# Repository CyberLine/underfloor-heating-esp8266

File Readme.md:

# ESP8266 WiFi based underfloor heating control

### Hardware

See: [Hardware.md](Hardware.md)

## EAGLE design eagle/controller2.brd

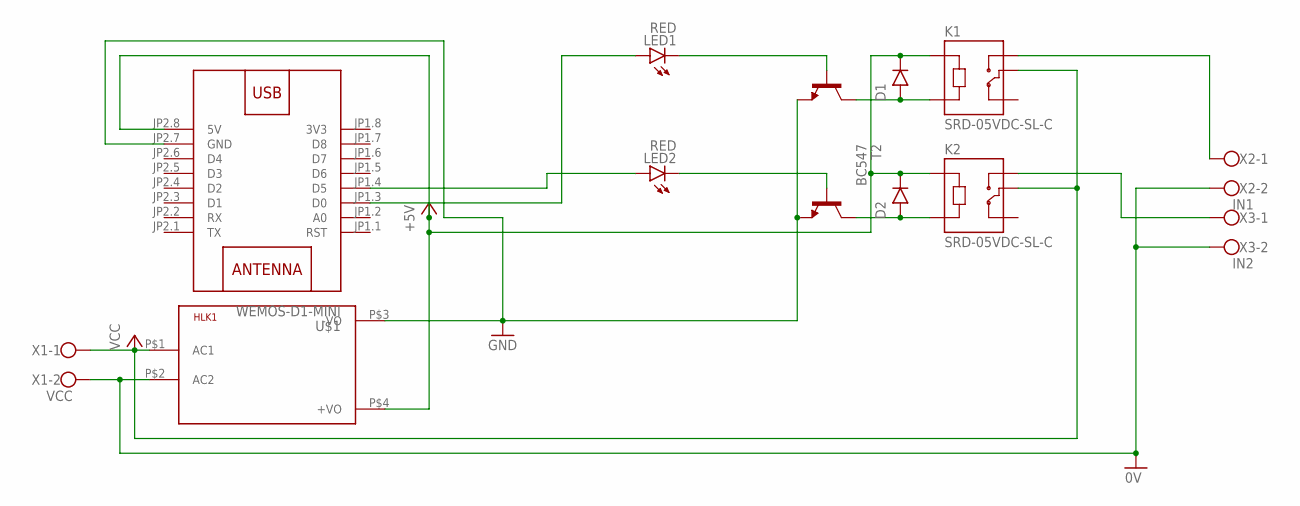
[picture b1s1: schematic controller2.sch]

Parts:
D1, D2: 1N4001; DO41-10
HLK1: HLK-PM013W; HLK-PM01
K1, K2: SRD-05VDC-SL-C; RELAY_SRD-05VDC-SL-C
LED1, LED2: RED; LED3MM
T1, T2: BC547; TO92
U$1: WEMOS-D1-MINI
X1: VCC; W237-102
X2: IN1; W237-102
X3: IN2; W237-102

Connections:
0V: HLK1.P$2 (AC2), X1.2, X2.2, X3.2
3V3: U$1.JP1.8 (3V3)
+5V: D1.C (CATHODE), D2.C (CATHODE), HLK1.P$4 (+VO), K1.A1, K2.A1, U$1.JP2.8 (5V)
GND: HLK1.P$3 (-VO), T1.1 (E), T2.1 (E), U$1.JP2.7 (GND)
unnamed: D1.A (ANODE), K1.A2, T1.3 (C)
unnamed: K1.NO, X2.1
unnamed: D2.A (ANODE), K2.A2, T2.3 (C)
unnamed: LED2.K (C), T2.2 (B)
unnamed: LED1.K (C), T1.2 (B)
unnamed: K2.NO, X3.1
unnamed: LED2.A, U$1.JP1.4 (D5)
unnamed: LED1.A, U$1.JP1.3 (D0)
VCC: HLK1.P$1 (AC1), K1.COM, K2.COM, X1.1

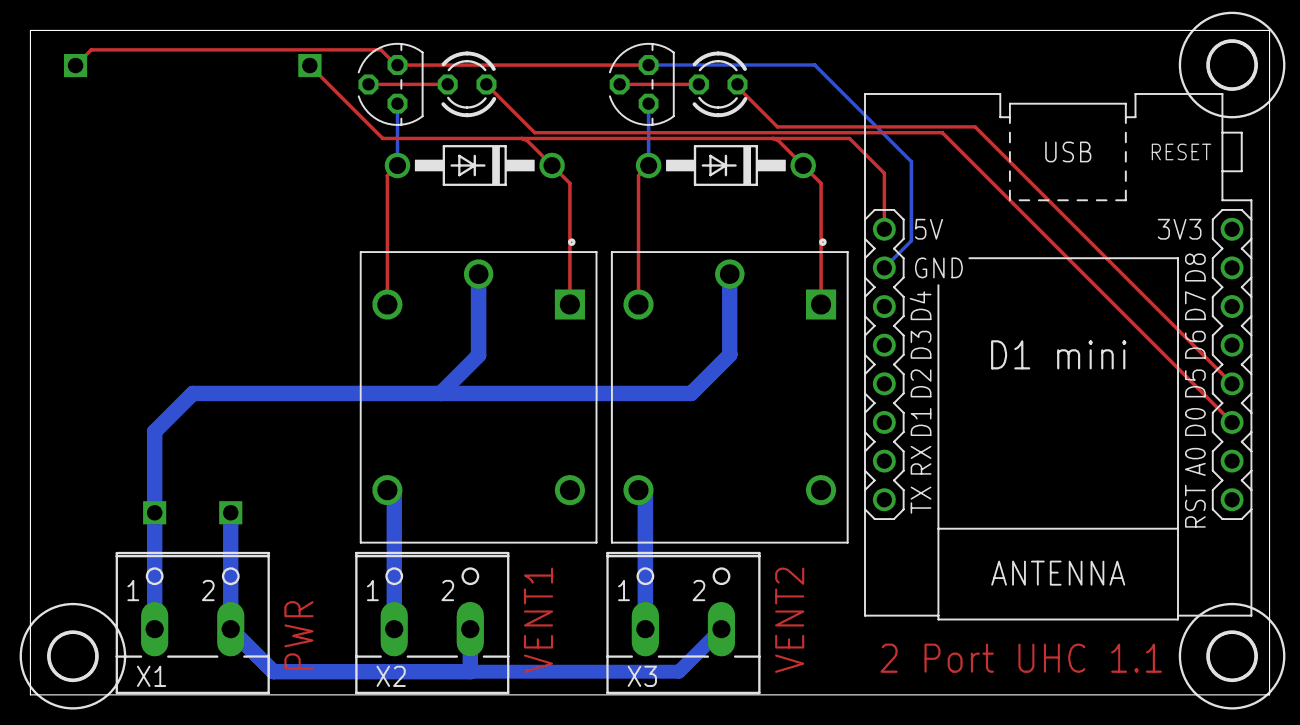
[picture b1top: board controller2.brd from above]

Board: 2 copper layers, 81.5 x 43.7 mm, 16 parts (0 on the bottom side), 12 nets.

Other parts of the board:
U$2, U$3, U$4: 3,0

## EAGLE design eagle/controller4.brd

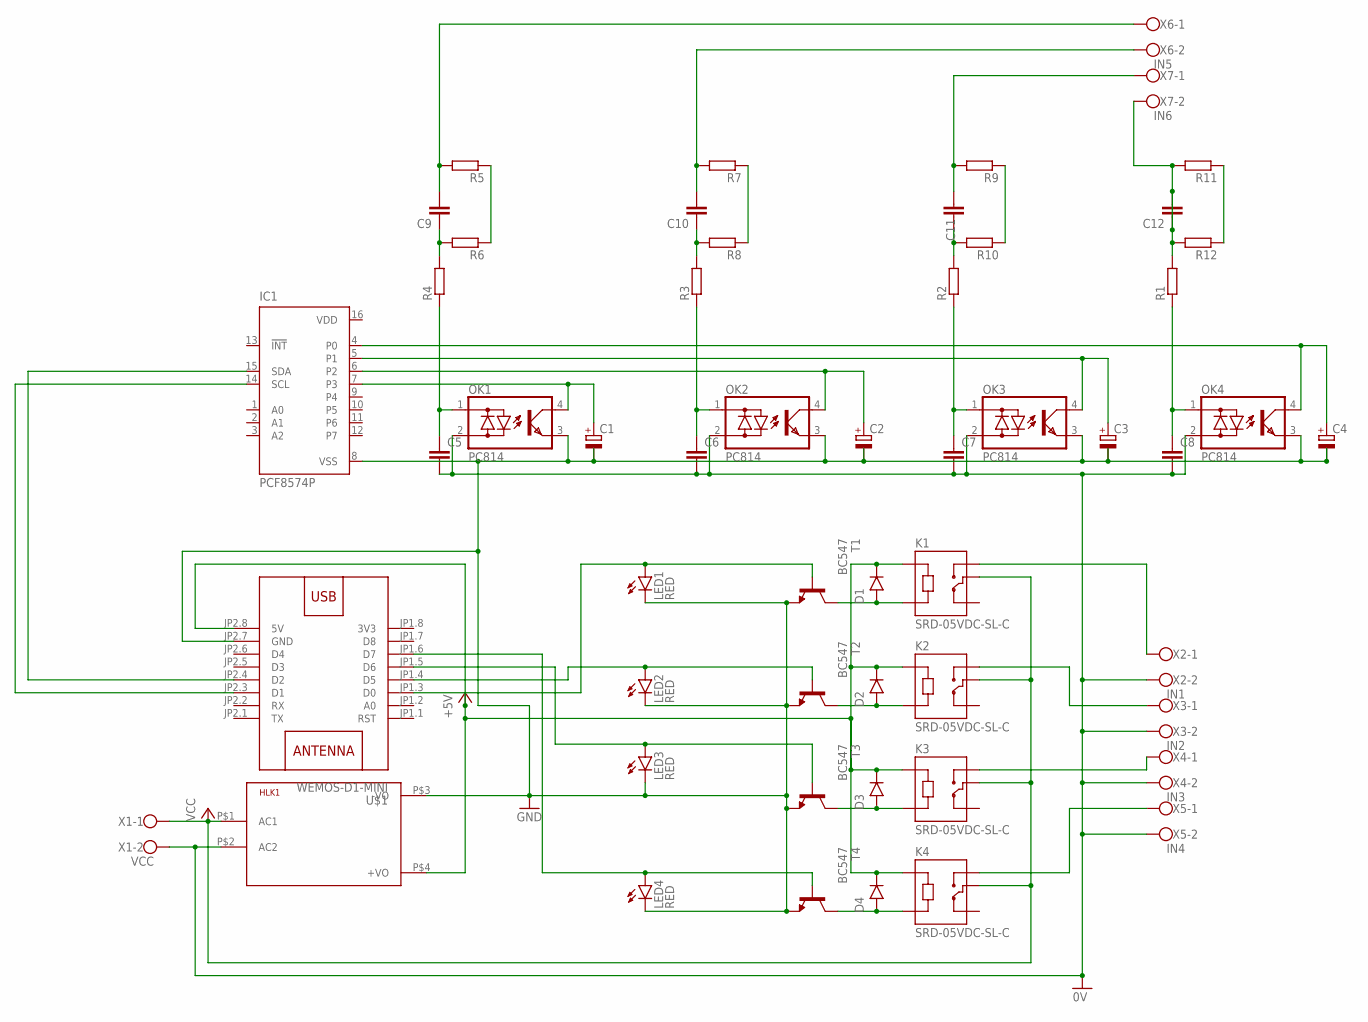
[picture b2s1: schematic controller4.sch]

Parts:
C1, C2, C3, C4: CPOL-EUE5-5; E5-5
C5, C6, C7, C8, C9, C10, C11, C12: C-EU025-024X044; C025-024X044
D1, D2, D3, D4: 1N4001; DO41-10
HLK1: HLK-PM013W; HLK-PM01
IC1: PCF8574P; DIL16
K1, K2, K3, K4: SRD-05VDC-SL-C; RELAY_SRD-05VDC-SL-C
LED1, LED2, LED3, LED4: RED; LED3MM
OK1, OK2, OK3, OK4: PC814; DIL04
R1, R2, R3, R4, R5, R6, R7, R8, R9, R10, R11, R12: R-EU_0204/5; 0204/5
T1, T2, T3, T4: BC547; TO92
U$1: WEMOS-D1-MINI
X1: VCC; W237-102
X2: IN1; W237-102
X3: IN2; W237-102
X4: IN3; W237-102
X5: IN4; W237-102
X6: IN5; W237-102
X7: IN6; W237-102

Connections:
0V: C5.2, C6.2, C7.2, C8.2, HLK1.P$2 (AC2), OK1.2 (AC2), OK2.2 (AC2), OK3.2 (AC2), OK4.2 (AC2), X1.2, X2.2, X3.2, X4.2, X5.2
3V3: U$1.JP1.8 (3V3)
+5V: D1.C (CATHODE), D2.C (CATHODE), D3.C (CATHODE), D4.C (CATHODE), HLK1.P$4 (+VO), K1.A1, K2.A1, K3.A1, K4.A1, U$1.JP2.8 (5V)
GND: C1.-, C2.-, C3.-, C4.-, HLK1.P$3 (-VO), IC1.8 (VSS), LED1.K (C), LED2.K (C), LED3.K (C), LED4.K (C), OK1.3 (E), OK2.3 (E), OK3.3 (E), OK4.3 (E), T1.1 (E), T2.1 (E), T3.1 (E), T4.1 (E), U$1.JP2.7 (GND)
unnamed: D1.A (ANODE), K1.A2, T1.3 (C)
unnamed: K1.NO, X2.1
unnamed: D2.A (ANODE), K2.A2, T2.3 (C)
unnamed: D3.A (ANODE), K3.A2, T3.3 (C)
unnamed: D4.A (ANODE), K4.A2, T4.3 (C)
unnamed: C1.+, IC1.7 (P3), OK1.4 (C)
unnamed: C2.+, IC1.6 (P2), OK2.4 (C)
unnamed: C3.+, IC1.5 (P1), OK3.4 (C)
unnamed: C4.+, IC1.4 (P0), OK4.4 (C)
unnamed: C9.1, R4.2, R6.2
unnamed: K2.NO, X3.1
unnamed: K3.NO, X4.1
unnamed: K4.NO, X5.1
unnamed: LED2.A, T2.2 (B), U$1.JP1.4 (D5)
unnamed: LED1.A, T1.2 (B), U$1.JP1.3 (D0)
unnamed: LED4.A, T4.2 (B), U$1.JP1.6 (D7)
unnamed: IC1.14 (SCL), U$1.JP2.3 (D1)
unnamed: IC1.15 (SDA), U$1.JP2.4 (D2)
unnamed: LED3.A, T3.2 (B), U$1.JP1.5 (D6)
unnamed: C10.1, R3.2, R8.2
unnamed: C11.1, R2.2, R10.2
unnamed: C8.1, OK4.1 (AC1), R1.1
unnamed: C11.2, R9.2, X7.1
unnamed: C10.2, R7.2, X6.2
unnamed: C9.2, R5.2, X6.1
unnamed: R5.1, R6.1
unnamed: C12.1, C12.2, R1.2, R11.2, R12.2, X7.2
unnamed: C7.1, OK3.1 (AC1), R2.1
unnamed: C6.1, OK2.1 (AC1), R3.1
unnamed: C5.1, OK1.1 (AC1), R4.1
unnamed: R7.1, R8.1
unnamed: R9.1, R10.1
unnamed: R11.1, R12.1
VCC: HLK1.P$1 (AC1), K1.COM, K2.COM, K3.COM, K4.COM, X1.1
VDD: IC1.16 (VDD)

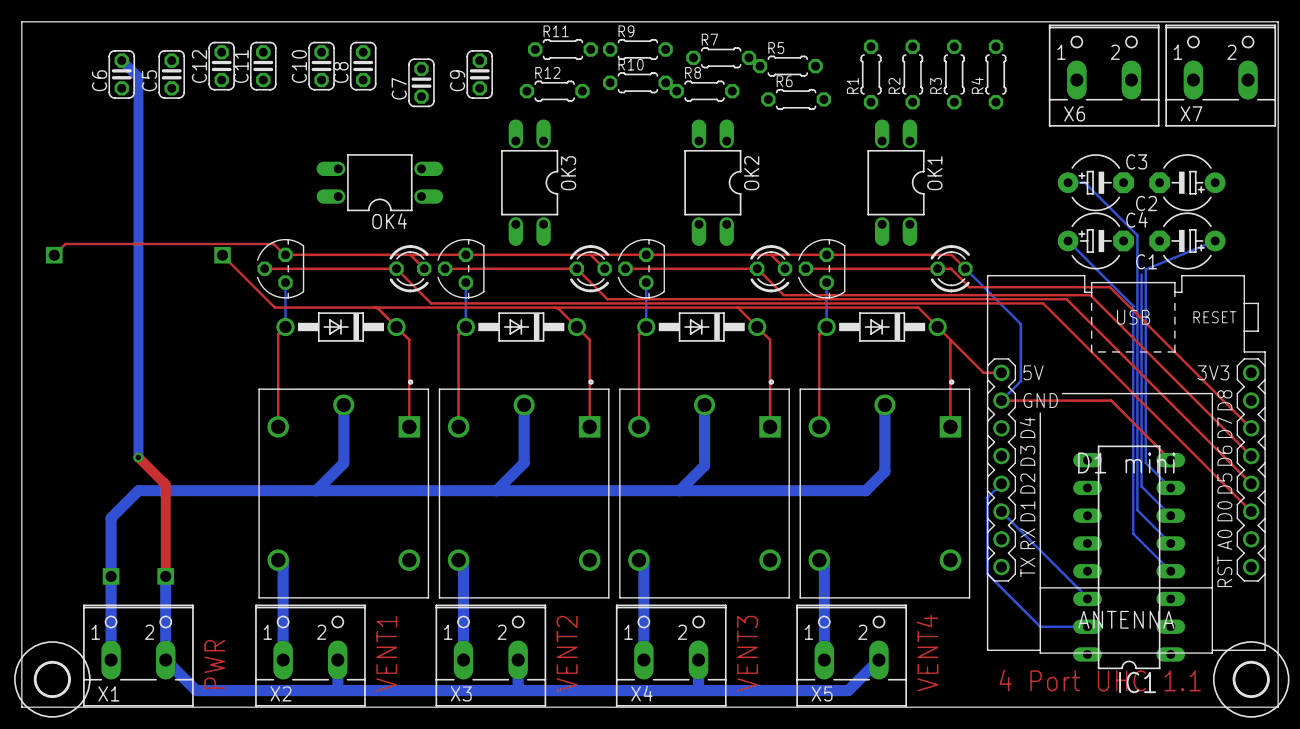
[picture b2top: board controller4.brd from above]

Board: 2 copper layers, 115.0 x 62.7 mm, 56 parts (0 on the bottom side), 37 nets.

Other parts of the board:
U$2, U$3: 3,0

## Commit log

2021-01-07 initial WIP
2021-01-07 Initial Version
2021-01-07 Add different board version
2021-01-07 Add Readme
2021-01-07 Fix HW Parts
2021-01-15 refactoring
2021-01-15 adding first software
2021-01-15 cleanup ino
2021-01-15 change gitignore

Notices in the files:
parts and their libraries:
diy-modules: Released under the Creative Commons Attribution 4.0 International License: http://creativecommons.org/licenses/by/4.0
